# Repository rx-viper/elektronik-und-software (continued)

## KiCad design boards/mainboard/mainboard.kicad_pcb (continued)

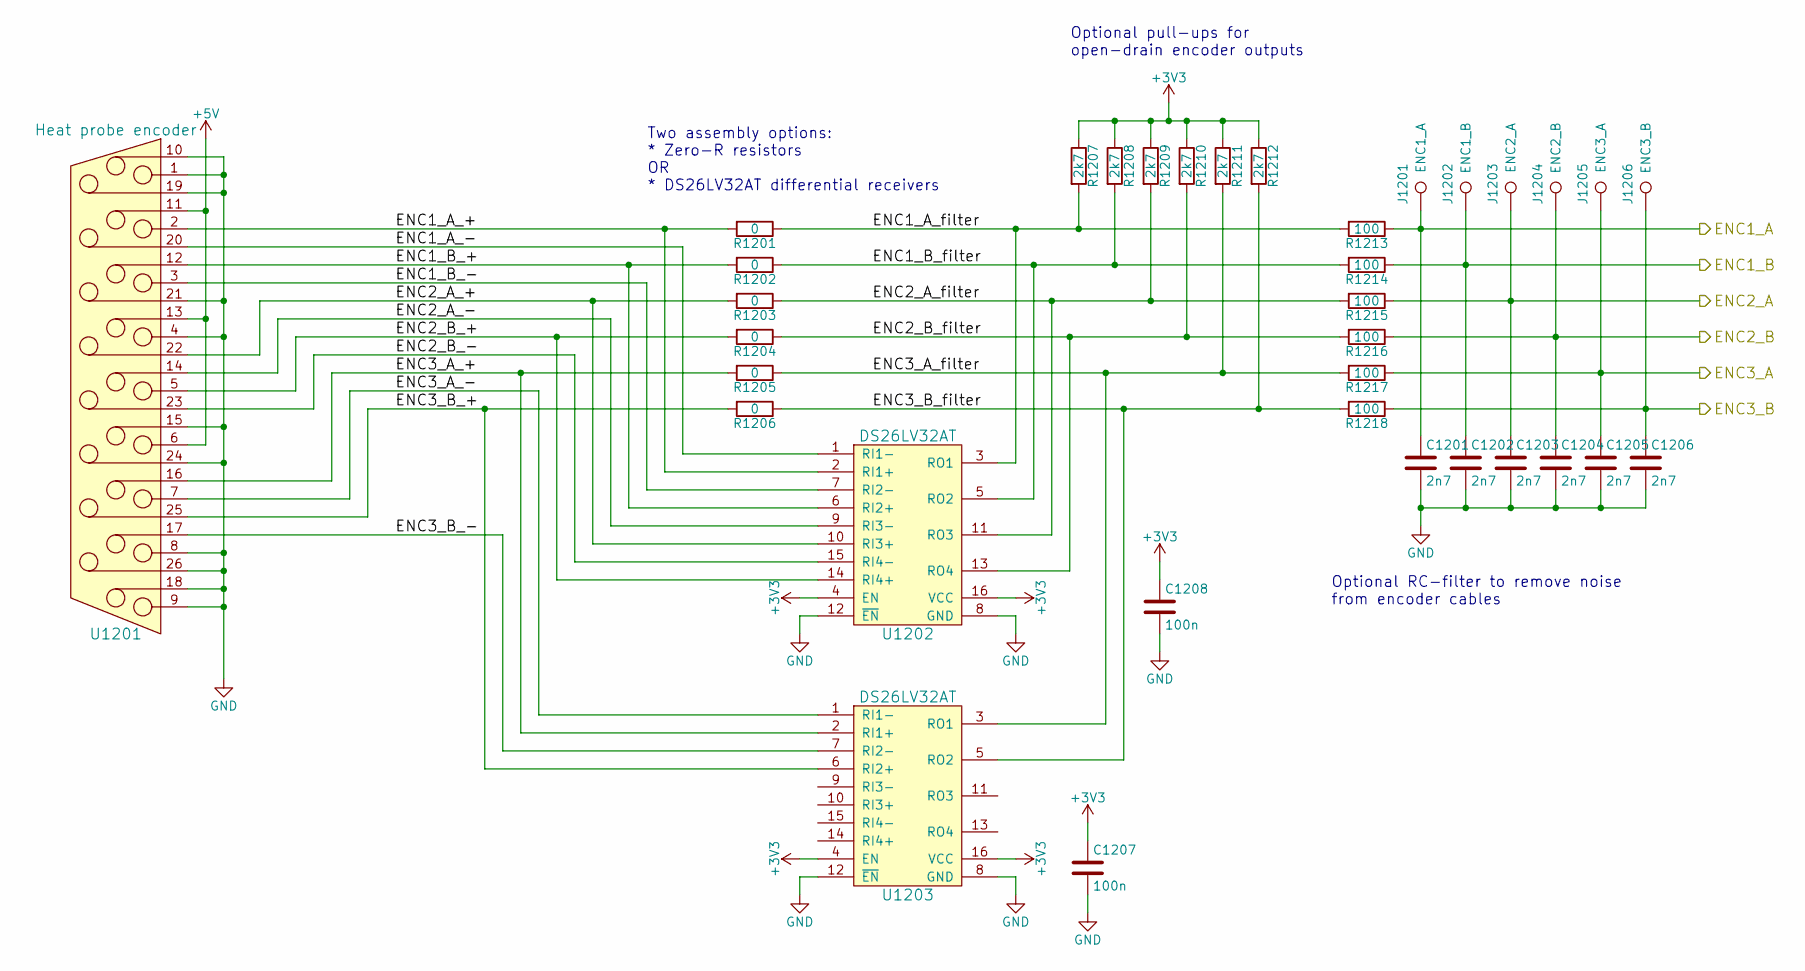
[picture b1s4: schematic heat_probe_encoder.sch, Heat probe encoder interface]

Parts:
C1201, C1202, C1203, C1204, C1205, C1206: 2n7; C_0603
C1207, C1208: 100n; C_0603
J1201: ENC1_A; Measurement_Point_Round-SMD-Pad_Small
J1202: ENC1_B; Measurement_Point_Round-SMD-Pad_Small
J1203: ENC2_A; Measurement_Point_Round-SMD-Pad_Small
J1204: ENC2_B; Measurement_Point_Round-SMD-Pad_Small
J1205: ENC3_A; Measurement_Point_Round-SMD-Pad_Small
J1206: ENC3_B; Measurement_Point_Round-SMD-Pad_Small
R1201, R1202, R1203, R1204, R1205, R1206: 0; R_0603
R1207, R1208, R1209, R1210, R1211, R1212: 2k7; R_0603
R1213, R1214, R1215, R1216, R1217, R1218: 100; R_0603
U1201: Heat probe encoder; D-Sub_HD_26_F
U1202, U1203: DS26LV32AT; SOIC-16_3.9x9.9mm_Pitch1.27mm

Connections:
+3V3: C1207.1, C1208.1, R1207.1, R1208.1, R1209.1, R1210.1, R1211.1, R1212.1, U1202.4 (EN), U1202.16 (VCC), U1203.4 (EN), U1203.16 (VCC); also elsewhere on the board
+5V: U1201.6, U1201.11, U1201.13; also elsewhere on the board
/Heat_Probe_Encoder/ENC1_A: C1201.1, J1201.1, R1213.1; also elsewhere on the board
/Heat_Probe_Encoder/ENC1_A_+: R1201.2, U1201.2, U1202.2 (RI1+)
/Heat_Probe_Encoder/ENC1_A_-: U1201.20, U1202.1 (RI1-)
/Heat_Probe_Encoder/ENC1_A_filter: R1201.1, R1207.2, R1213.2, U1202.3 (RO1)
/Heat_Probe_Encoder/ENC1_B: C1202.1, J1202.1, R1214.1; also elsewhere on the board
/Heat_Probe_Encoder/ENC1_B_+: R1202.2, U1201.12, U1202.6 (RI2+)
/Heat_Probe_Encoder/ENC1_B_-: U1201.3, U1202.7 (RI2-)
/Heat_Probe_Encoder/ENC1_B_filter: R1202.1, R1208.2, R1214.2, U1202.5 (RO2)
/Heat_Probe_Encoder/ENC2_A: C1203.1, J1203.1, R1215.1; also elsewhere on the board
/Heat_Probe_Encoder/ENC2_A_+: R1203.2, U1201.22, U1202.10 (RI3+)
/Heat_Probe_Encoder/ENC2_A_-: U1201.14, U1202.9 (RI3-)
/Heat_Probe_Encoder/ENC2_A_filter: R1203.1, R1209.2, R1215.2, U1202.11 (RO3)
/Heat_Probe_Encoder/ENC2_B: C1204.1, J1204.1, R1216.1; also elsewhere on the board
/Heat_Probe_Encoder/ENC2_B_+: R1204.2, U1201.5, U1202.14 (RI4+)
/Heat_Probe_Encoder/ENC2_B_-: U1201.23, U1202.15 (RI4-)
/Heat_Probe_Encoder/ENC2_B_filter: R1204.1, R1210.2, R1216.2, U1202.13 (RO4)
/Heat_Probe_Encoder/ENC3_A: C1205.1, J1205.1, R1217.1; also elsewhere on the board
/Heat_Probe_Encoder/ENC3_A_+: R1205.2, U1201.16, U1203.2 (RI1+)
/Heat_Probe_Encoder/ENC3_A_-: U1201.7, U1203.1 (RI1-)
/Heat_Probe_Encoder/ENC3_A_filter: R1205.1, R1211.2, R1217.2, U1203.3 (RO1)
/Heat_Probe_Encoder/ENC3_B: C1206.1, J1206.1, R1218.1; also elsewhere on the board
/Heat_Probe_Encoder/ENC3_B_+: R1206.2, U1201.25, U1203.6 (RI2+)
/Heat_Probe_Encoder/ENC3_B_-: U1201.17, U1203.7 (RI2-)
/Heat_Probe_Encoder/ENC3_B_filter: R1206.1, R1212.2, R1218.2, U1203.5 (RO2)
GND: C1201.2, C1202.2, C1203.2, C1204.2, C1205.2, C1206.2, C1207.2, C1208.2, U1201.1, U1201.4, U1201.8, U1201.9, U1201.10, U1201.15, U1201.18, U1201.19, U1201.21, U1201.24, U1201.26, U1202.8 (GND), U1202.12 (~EN), U1203.8 (GND), U1203.12 (~EN); also elsewhere on the board

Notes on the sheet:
Optional pull-ups for open-drain encoder outputs
Optional RC-filter to remove noise from encoder cables
Two assembly options: * Zero-R resistors OR * DS26LV32AT differential receivers

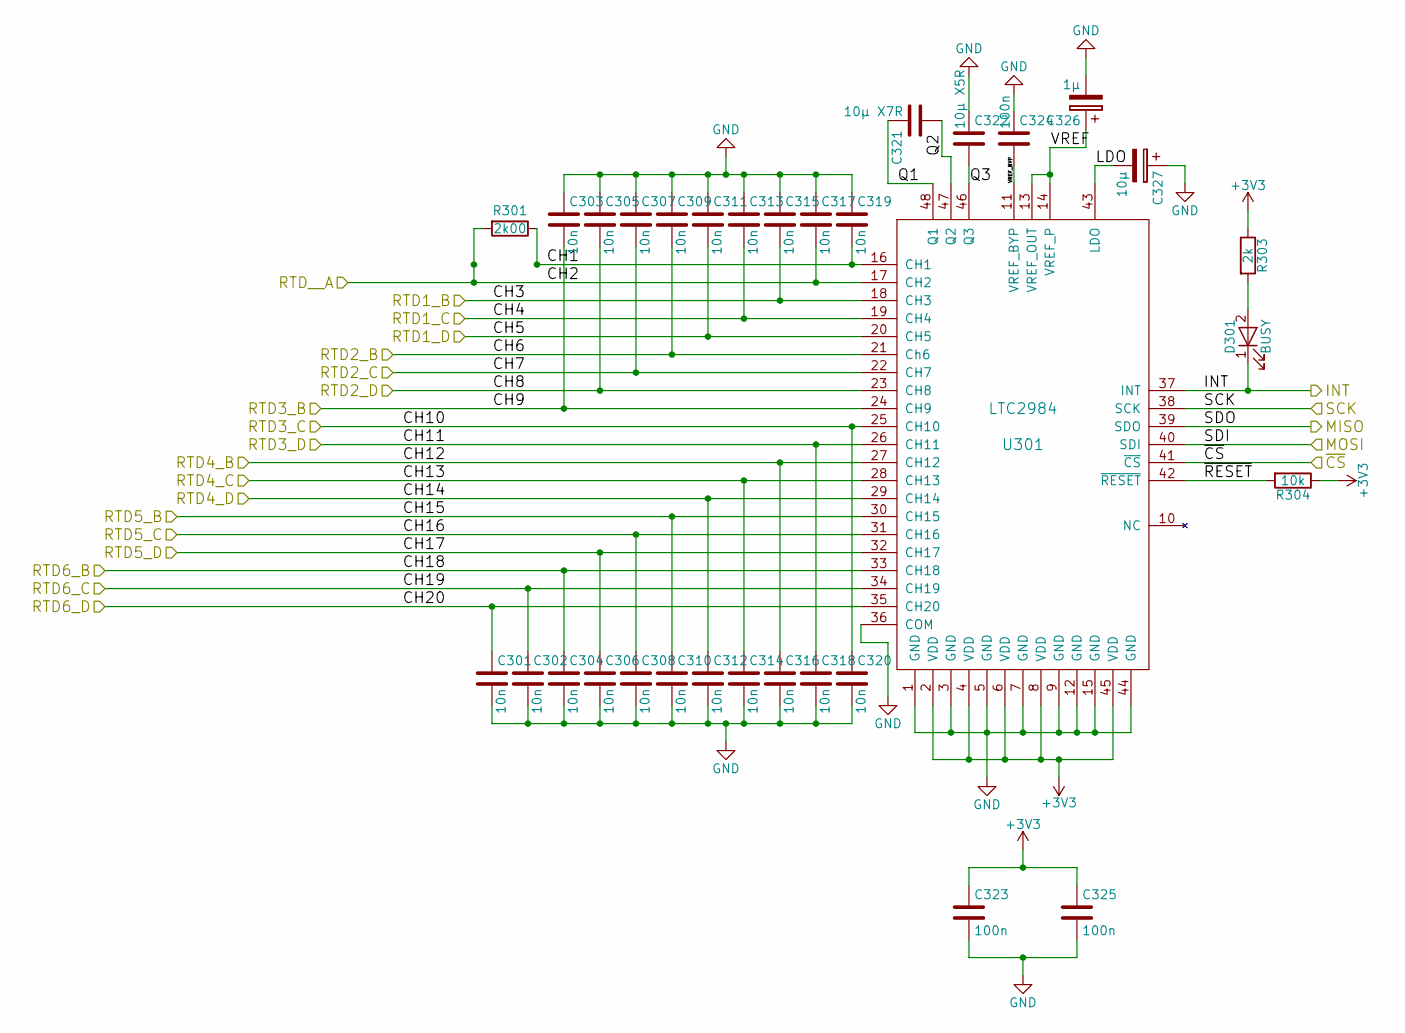
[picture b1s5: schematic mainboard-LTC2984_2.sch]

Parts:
C301, C302, C303, C304, C305, C306, C307, C308, C309, C310, C311, C312, C313, C314, C315, C316, C317, C318, C319, C320: 10n; C_0603
C321: 10µ X7R; C_0805
C322: 10µ X5R; C_0805
C323, C324, C325: 100n; C_0603
C326: 1µ; C_0805
C327: 10µ; C_0805
D301: BUSY; LED_0603
R301: 2k00; R_1206
R303: 2k; R_0603
R304: 10k; R_0603
U301: LTC2984; LQFP-48_7x7mm_Pitch0.5mm

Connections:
+3V3: C323.1, C325.1, R303.1, R304.1, U301.2 (VDD), U301.4 (VDD), U301.6 (VDD), U301.8 (VDD), U301.45 (VDD); also elsewhere on the board
/Mainboard_Temp_Sensors/INT2: D301.1 (K), U301.37 (INT)
/Mainboard_Temp_Sensors/Mainboard_LTC2984_2/CH1: C319.2, R301.1, U301.16 (CH1)
/Mainboard_Temp_Sensors/Mainboard_LTC2984_2/LDO: C327.2, U301.43 (LDO)
/Mainboard_Temp_Sensors/Mainboard_LTC2984_2/Q1: C321.2, U301.48 (Q1)
/Mainboard_Temp_Sensors/Mainboard_LTC2984_2/Q2: C321.1, U301.47 (Q2)
/Mainboard_Temp_Sensors/Mainboard_LTC2984_2/Q3: C322.2, U301.46 (Q3)
/Mainboard_Temp_Sensors/Mainboard_LTC2984_2/VREF: C326.1, U301.13 (VREF_OUT), U301.14 (VREF_P)
/Mainboard_Temp_Sensors/Mainboard_LTC2984_2/VREF_BYP: C324.2, U301.11 (VREF_BYP)
/Mainboard_Temp_Sensors/Mainboard_LTC2984_2/~RESET: R304.2, U301.42 (~RESET)
/Mainboard_Temp_Sensors/SPI1_CS2: U301.41 (~CS); also elsewhere on the board
/Mainboard_Temp_Sensors/SPI1_MISO: U301.39 (SDO); also elsewhere on the board
/Mainboard_Temp_Sensors/SPI1_MOSI: U301.40 (SDI); also elsewhere on the board
/Mainboard_Temp_Sensors/SPI1_SCK: U301.38 (SCK); also elsewhere on the board
/Mainboard_Temp_Sensors/T2_RTD1_A: C317.2, R301.2, U301.17 (CH2); also elsewhere on the board
/Mainboard_Temp_Sensors/T2_RTD1_B: C315.2, U301.18 (CH3); also elsewhere on the board
/Mainboard_Temp_Sensors/T2_RTD1_C: C313.2, U301.19 (CH4); also elsewhere on the board
/Mainboard_Temp_Sensors/T2_RTD1_D: C311.2, U301.20 (CH5); also elsewhere on the board
/Mainboard_Temp_Sensors/T2_RTD2_B: C309.2, U301.21 (Ch6); also elsewhere on the board
/Mainboard_Temp_Sensors/T2_RTD2_C: C307.2, U301.22 (CH7); also elsewhere on the board
/Mainboard_Temp_Sensors/T2_RTD2_D: C305.2, U301.23 (CH8); also elsewhere on the board
/Mainboard_Temp_Sensors/T2_RTD3_B: C303.2, U301.24 (CH9); also elsewhere on the board
/Mainboard_Temp_Sensors/T2_RTD3_C: C320.1, U301.25 (CH10); also elsewhere on the board
/Mainboard_Temp_Sensors/T2_RTD3_D: C318.1, U301.26 (CH11); also elsewhere on the board
/Mainboard_Temp_Sensors/T2_RTD4_B: C316.1, U301.27 (CH12); also elsewhere on the board
/Mainboard_Temp_Sensors/T2_RTD4_C: C314.1, U301.28 (CH13); also elsewhere on the board
/Mainboard_Temp_Sensors/T2_RTD4_D: C312.1, U301.29 (CH14); also elsewhere on the board
/Mainboard_Temp_Sensors/T2_RTD5_B: C310.1, U301.30 (CH15); also elsewhere on the board
/Mainboard_Temp_Sensors/T2_RTD5_C: C308.1, U301.31 (CH16); also elsewhere on the board
/Mainboard_Temp_Sensors/T2_RTD5_D: C306.1, U301.32 (CH17); also elsewhere on the board
/Mainboard_Temp_Sensors/T2_RTD6_B: C304.1, U301.33 (CH18); also elsewhere on the board
/Mainboard_Temp_Sensors/T2_RTD6_C: C302.1, U301.34 (CH19); also elsewhere on the board
/Mainboard_Temp_Sensors/T2_RTD6_D: C301.1, U301.35 (CH20); also elsewhere on the board
GND: C301.2, C302.2, C303.1, C304.2, C305.1, C306.2, C307.1, C308.2, C309.1, C310.2, C311.1, C312.2, C313.1, C314.2, C315.1, C316.2, C317.1, C318.2, C319.1, C320.2, C322.1, C323.2, C324.1, C325.2, C326.2, C327.1, U301.1 (GND), U301.3 (GND), U301.5 (GND), U301.7 (GND), U301.9 (GND), U301.12 (GND), U301.15 (GND), U301.36 (COM), U301.44 (GND); also elsewhere on the board
unnamed: D301.2 (A), R303.2

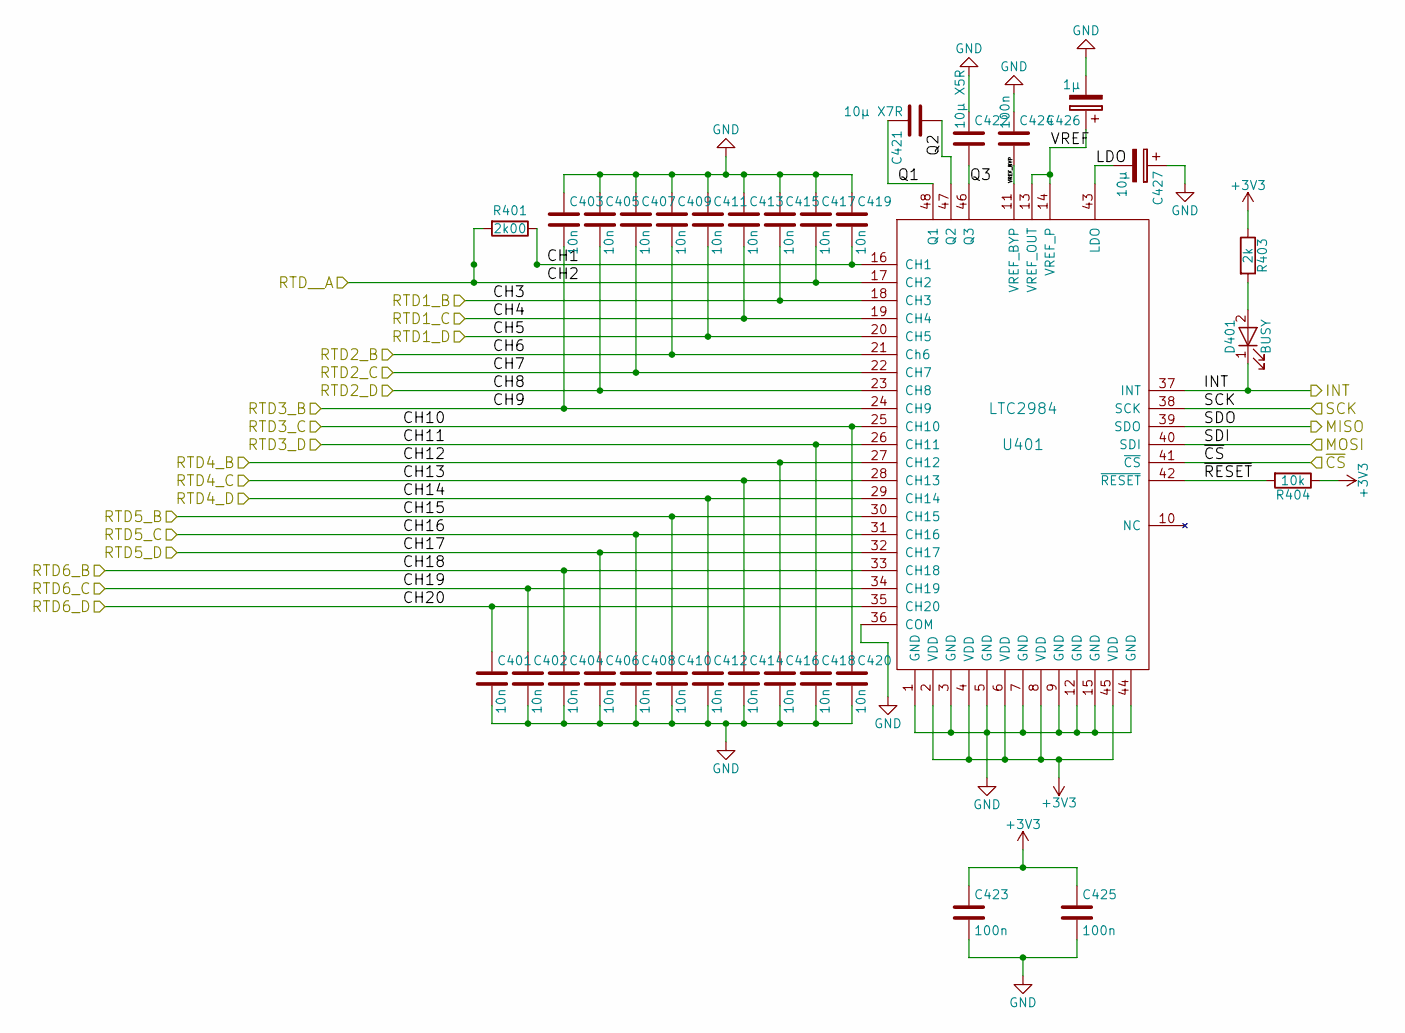
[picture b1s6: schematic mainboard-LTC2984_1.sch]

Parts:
C401, C402, C403, C404, C405, C406, C407, C408, C409, C410, C411, C412, C413, C414, C415, C416, C417, C418, C419, C420: 10n; C_0603
C421: 10µ X7R; C_0805
C422: 10µ X5R; C_0805
C423, C424, C425: 100n; C_0603
C426: 1µ; C_0805
C427: 10µ; C_0805
D401: BUSY; LED_0603
R401: 2k00; R_1206
R403: 2k; R_0603
R404: 10k; R_0603
U401: LTC2984; LQFP-48_7x7mm_Pitch0.5mm

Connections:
+3V3: C423.1, C425.1, R403.1, R404.1, U401.2 (VDD), U401.4 (VDD), U401.6 (VDD), U401.8 (VDD), U401.45 (VDD); also elsewhere on the board
/Mainboard_Temp_Sensors/INT1: D401.1 (K), U401.37 (INT)
/Mainboard_Temp_Sensors/Mainboard_LTC2984_1/CH1: C419.2, R401.1, U401.16 (CH1)
/Mainboard_Temp_Sensors/Mainboard_LTC2984_1/LDO: C427.2, U401.43 (LDO)
/Mainboard_Temp_Sensors/Mainboard_LTC2984_1/Q1: C421.2, U401.48 (Q1)
/Mainboard_Temp_Sensors/Mainboard_LTC2984_1/Q2: C421.1, U401.47 (Q2)
/Mainboard_Temp_Sensors/Mainboard_LTC2984_1/Q3: C422.2, U401.46 (Q3)
/Mainboard_Temp_Sensors/Mainboard_LTC2984_1/VREF: C426.1, U401.13 (VREF_OUT), U401.14 (VREF_P)
/Mainboard_Temp_Sensors/Mainboard_LTC2984_1/VREF_BYP: C424.2, U401.11 (VREF_BYP)
/Mainboard_Temp_Sensors/Mainboard_LTC2984_1/~RESET: R404.2, U401.42 (~RESET)
/Mainboard_Temp_Sensors/SPI1_CS1: U401.41 (~CS); also elsewhere on the board
/Mainboard_Temp_Sensors/SPI1_MISO: U401.39 (SDO); also elsewhere on the board
/Mainboard_Temp_Sensors/SPI1_MOSI: U401.40 (SDI); also elsewhere on the board
/Mainboard_Temp_Sensors/SPI1_SCK: U401.38 (SCK); also elsewhere on the board
/Mainboard_Temp_Sensors/T1_RTD1_A: C417.2, R401.2, U401.17 (CH2); also elsewhere on the board
/Mainboard_Temp_Sensors/T1_RTD1_B: C415.2, U401.18 (CH3); also elsewhere on the board
/Mainboard_Temp_Sensors/T1_RTD1_C: C413.2, U401.19 (CH4); also elsewhere on the board
/Mainboard_Temp_Sensors/T1_RTD1_D: C411.2, U401.20 (CH5); also elsewhere on the board
/Mainboard_Temp_Sensors/T1_RTD2_B: C409.2, U401.21 (Ch6); also elsewhere on the board
/Mainboard_Temp_Sensors/T1_RTD2_C: C407.2, U401.22 (CH7); also elsewhere on the board
/Mainboard_Temp_Sensors/T1_RTD2_D: C405.2, U401.23 (CH8); also elsewhere on the board
/Mainboard_Temp_Sensors/T1_RTD3_B: C403.2, U401.24 (CH9); also elsewhere on the board
/Mainboard_Temp_Sensors/T1_RTD3_C: C420.1, U401.25 (CH10); also elsewhere on the board
/Mainboard_Temp_Sensors/T1_RTD3_D: C418.1, U401.26 (CH11); also elsewhere on the board
/Mainboard_Temp_Sensors/T1_RTD4_B: C416.1, U401.27 (CH12); also elsewhere on the board
/Mainboard_Temp_Sensors/T1_RTD4_C: C414.1, U401.28 (CH13); also elsewhere on the board
/Mainboard_Temp_Sensors/T1_RTD4_D: C412.1, U401.29 (CH14); also elsewhere on the board
/Mainboard_Temp_Sensors/T1_RTD5_B: C410.1, U401.30 (CH15); also elsewhere on the board
/Mainboard_Temp_Sensors/T1_RTD5_C: C408.1, U401.31 (CH16); also elsewhere on the board
/Mainboard_Temp_Sensors/T1_RTD5_D: C406.1, U401.32 (CH17); also elsewhere on the board
/Mainboard_Temp_Sensors/T1_RTD6_B: C404.1, U401.33 (CH18); also elsewhere on the board
/Mainboard_Temp_Sensors/T1_RTD6_C: C402.1, U401.34 (CH19); also elsewhere on the board
/Mainboard_Temp_Sensors/T1_RTD6_D: C401.1, U401.35 (CH20); also elsewhere on the board
GND: C401.2, C402.2, C403.1, C404.2, C405.1, C406.2, C407.1, C408.2, C409.1, C410.2, C411.1, C412.2, C413.1, C414.2, C415.1, C416.2, C417.1, C418.2, C419.1, C420.2, C422.1, C423.2, C424.1, C425.2, C426.2, C427.1, U401.1 (GND), U401.3 (GND), U401.5 (GND), U401.7 (GND), U401.9 (GND), U401.12 (GND), U401.15 (GND), U401.36 (COM), U401.44 (GND); also elsewhere on the board
unnamed: D401.2 (A), R403.2

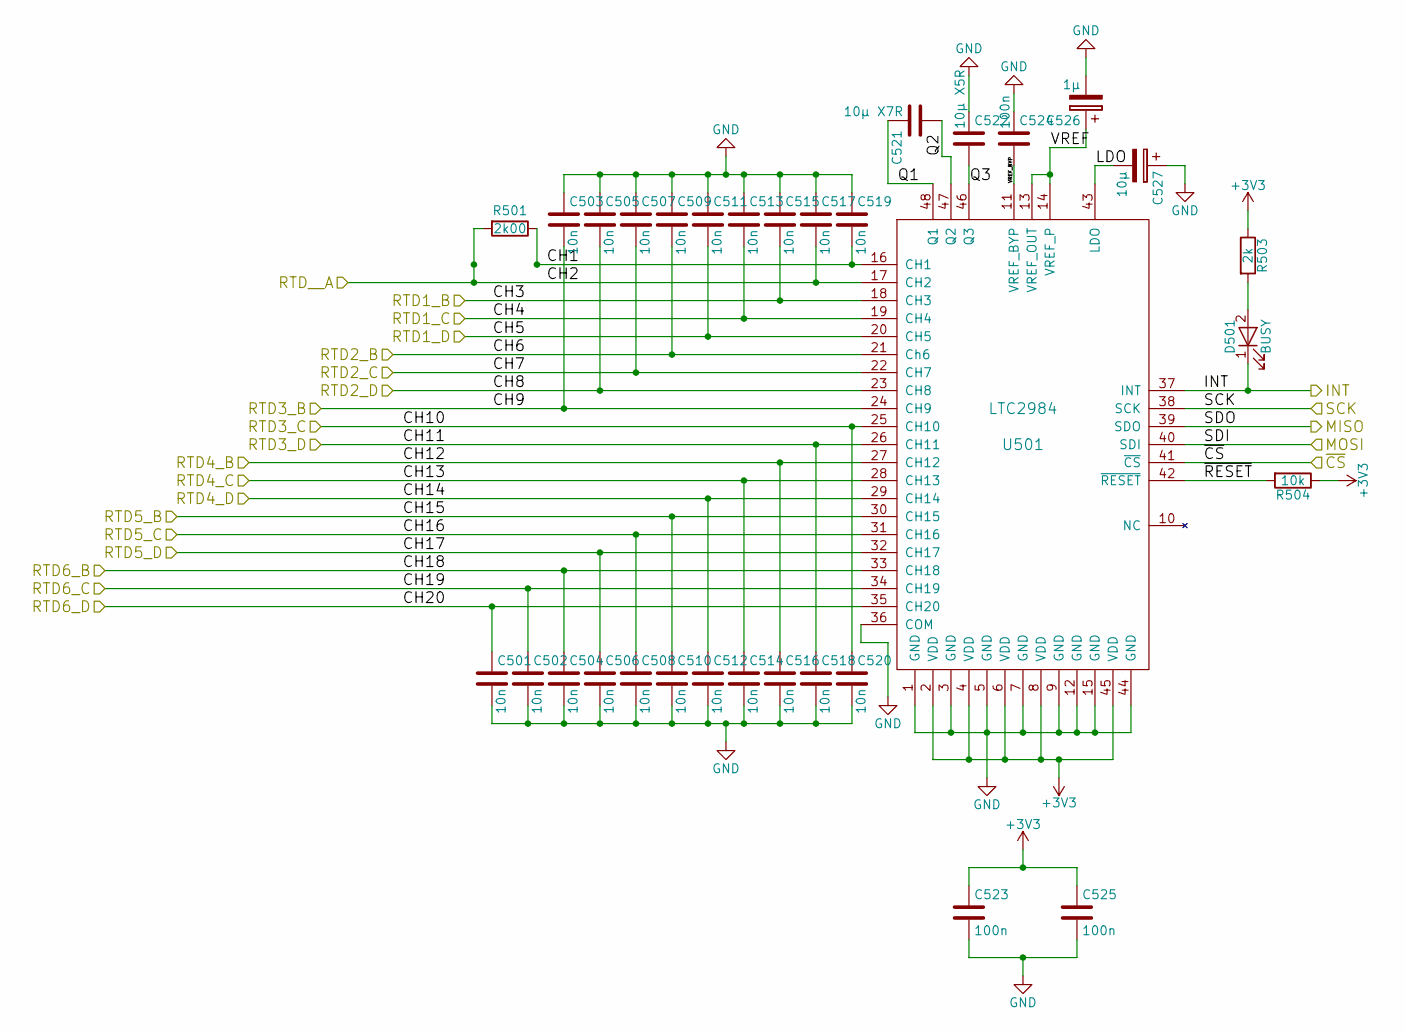
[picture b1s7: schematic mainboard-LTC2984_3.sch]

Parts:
C501, C502, C503, C504, C505, C506, C507, C508, C509, C510, C511, C512, C513, C514, C515, C516, C517, C518, C519, C520: 10n; C_0603
C521: 10µ X7R; C_0805
C522: 10µ X5R; C_0805
C523, C524, C525: 100n; C_0603
C526: 1µ; C_0805
C527: 10µ; C_0805
D501: BUSY; LED_0603
R501: 2k00; R_1206
R503: 2k; R_0603
R504: 10k; R_0603
U501: LTC2984; LQFP-48_7x7mm_Pitch0.5mm

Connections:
+3V3: C523.1, C525.1, R503.1, R504.1, U501.2 (VDD), U501.4 (VDD), U501.6 (VDD), U501.8 (VDD), U501.45 (VDD); also elsewhere on the board
/Mainboard_Temp_Sensors/INT3: D501.1 (K), U501.37 (INT)
/Mainboard_Temp_Sensors/Mainboard_LTC2984_3/CH1: C519.2, R501.1, U501.16 (CH1)
/Mainboard_Temp_Sensors/Mainboard_LTC2984_3/LDO: C527.2, U501.43 (LDO)
/Mainboard_Temp_Sensors/Mainboard_LTC2984_3/Q1: C521.2, U501.48 (Q1)
/Mainboard_Temp_Sensors/Mainboard_LTC2984_3/Q2: C521.1, U501.47 (Q2)
/Mainboard_Temp_Sensors/Mainboard_LTC2984_3/Q3: C522.2, U501.46 (Q3)
/Mainboard_Temp_Sensors/Mainboard_LTC2984_3/VREF: C526.1, U501.13 (VREF_OUT), U501.14 (VREF_P)
/Mainboard_Temp_Sensors/Mainboard_LTC2984_3/VREF_BYP: C524.2, U501.11 (VREF_BYP)
/Mainboard_Temp_Sensors/Mainboard_LTC2984_3/~RESET: R504.2, U501.42 (~RESET)
/Mainboard_Temp_Sensors/SPI1_CS3: U501.41 (~CS); also elsewhere on the board
/Mainboard_Temp_Sensors/SPI1_MISO: U501.39 (SDO); also elsewhere on the board
/Mainboard_Temp_Sensors/SPI1_MOSI: U501.40 (SDI); also elsewhere on the board
/Mainboard_Temp_Sensors/SPI1_SCK: U501.38 (SCK); also elsewhere on the board
/Mainboard_Temp_Sensors/T3_RTD1_A: C517.2, R501.2, U501.17 (CH2); also elsewhere on the board
/Mainboard_Temp_Sensors/T3_RTD1_B: C515.2, U501.18 (CH3); also elsewhere on the board
/Mainboard_Temp_Sensors/T3_RTD1_C: C513.2, U501.19 (CH4); also elsewhere on the board
/Mainboard_Temp_Sensors/T3_RTD1_D: C511.2, U501.20 (CH5); also elsewhere on the board
/Mainboard_Temp_Sensors/T3_RTD2_B: C509.2, U501.21 (Ch6); also elsewhere on the board
/Mainboard_Temp_Sensors/T3_RTD2_C: C507.2, U501.22 (CH7); also elsewhere on the board
/Mainboard_Temp_Sensors/T3_RTD2_D: C505.2, U501.23 (CH8); also elsewhere on the board
/Mainboard_Temp_Sensors/T3_RTD3_B: C503.2, U501.24 (CH9); also elsewhere on the board
/Mainboard_Temp_Sensors/T3_RTD3_C: C520.1, U501.25 (CH10); also elsewhere on the board
/Mainboard_Temp_Sensors/T3_RTD3_D: C518.1, U501.26 (CH11); also elsewhere on the board
/Mainboard_Temp_Sensors/T3_RTD4_B: C516.1, U501.27 (CH12); also elsewhere on the board
/Mainboard_Temp_Sensors/T3_RTD4_C: C514.1, U501.28 (CH13); also elsewhere on the board
/Mainboard_Temp_Sensors/T3_RTD4_D: C512.1, U501.29 (CH14); also elsewhere on the board
/Mainboard_Temp_Sensors/T3_RTD5_B: C510.1, U501.30 (CH15); also elsewhere on the board
/Mainboard_Temp_Sensors/T3_RTD5_C: C508.1, U501.31 (CH16); also elsewhere on the board
/Mainboard_Temp_Sensors/T3_RTD5_D: C506.1, U501.32 (CH17); also elsewhere on the board
/Mainboard_Temp_Sensors/T3_RTD6_B: C504.1, U501.33 (CH18); also elsewhere on the board
/Mainboard_Temp_Sensors/T3_RTD6_C: C502.1, U501.34 (CH19); also elsewhere on the board
/Mainboard_Temp_Sensors/T3_RTD6_D: C501.1, U501.35 (CH20); also elsewhere on the board
GND: C501.2, C502.2, C503.1, C504.2, C505.1, C506.2, C507.1, C508.2, C509.1, C510.2, C511.1, C512.2, C513.1, C514.2, C515.1, C516.2, C517.1, C518.2, C519.1, C520.2, C522.1, C523.2, C524.1, C525.2, C526.2, C527.1, U501.1 (GND), U501.3 (GND), U501.5 (GND), U501.7 (GND), U501.9 (GND), U501.12 (GND), U501.15 (GND), U501.36 (COM), U501.44 (GND); also elsewhere on the board
unnamed: D501.2 (A), R503.2

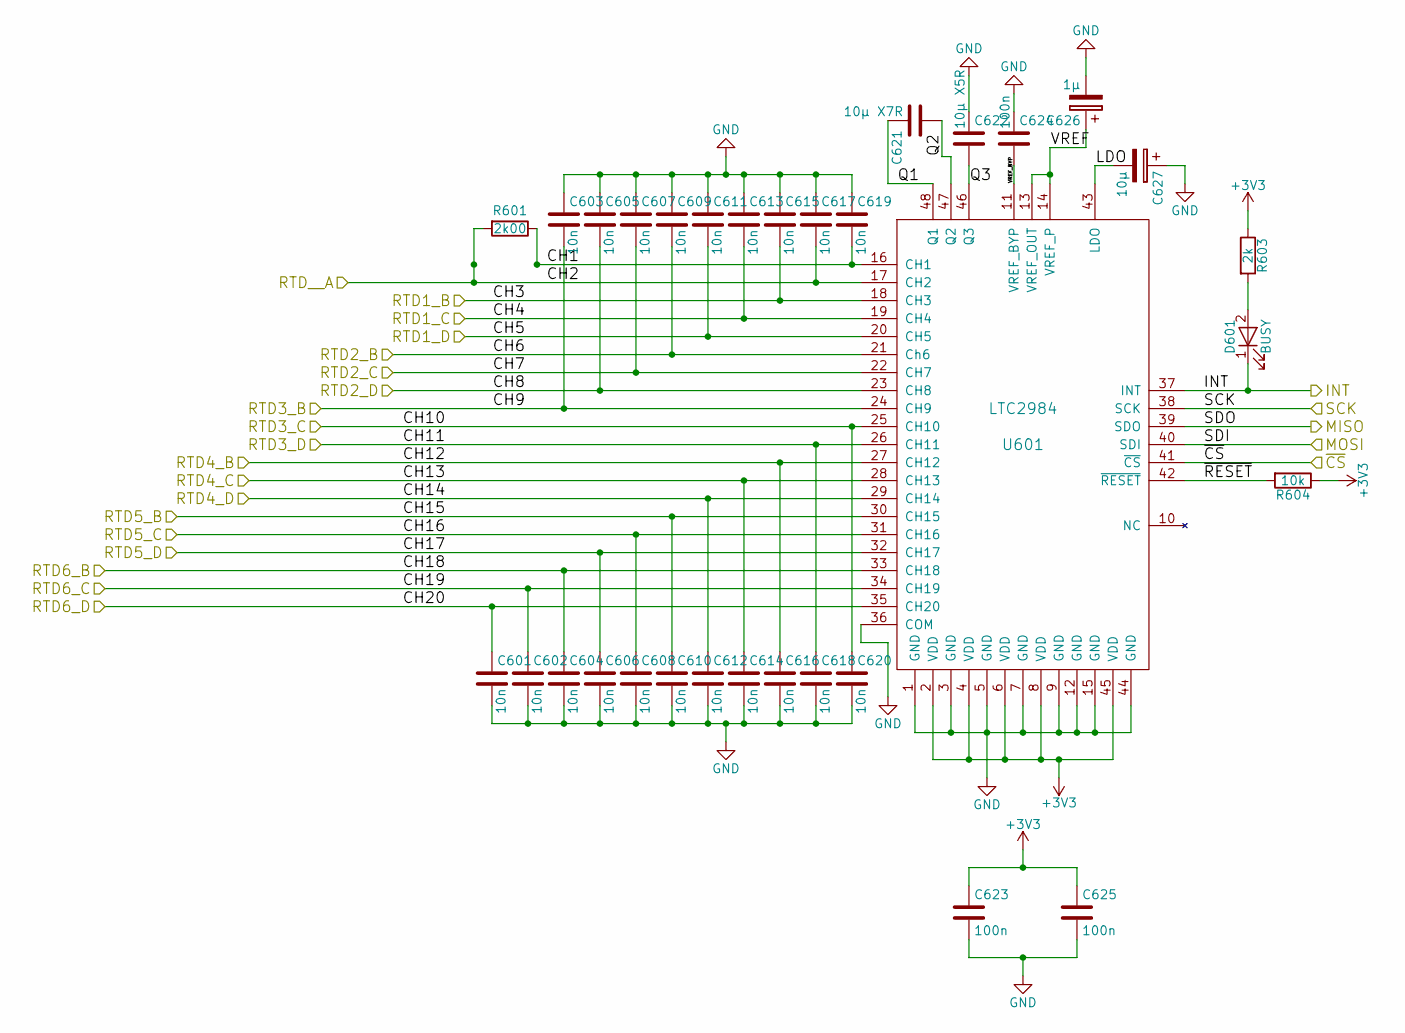
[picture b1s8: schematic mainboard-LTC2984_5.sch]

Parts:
C601, C602, C603, C604, C605, C606, C607, C608, C609, C610, C611, C612, C613, C614, C615, C616, C617, C618, C619, C620: 10n; C_0603
C621: 10µ X7R; C_0805
C622: 10µ X5R; C_0805
C623, C624, C625: 100n; C_0603
C626: 1µ; C_0805
C627: 10µ; C_0805
D601: BUSY; LED_0603
R601: 2k00; R_1206
R603: 2k; R_0603
R604: 10k; R_0603
U601: LTC2984; LQFP-48_7x7mm_Pitch0.5mm

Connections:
+3V3: C623.1, C625.1, R603.1, R604.1, U601.2 (VDD), U601.4 (VDD), U601.6 (VDD), U601.8 (VDD), U601.45 (VDD); also elsewhere on the board
/Mainboard_Temp_Sensors/INT5: D601.1 (K), U601.37 (INT)
/Mainboard_Temp_Sensors/Mainboard_LTC2984_5/CH1: C619.2, R601.1, U601.16 (CH1)
/Mainboard_Temp_Sensors/Mainboard_LTC2984_5/LDO: C627.2, U601.43 (LDO)
/Mainboard_Temp_Sensors/Mainboard_LTC2984_5/Q1: C621.2, U601.48 (Q1)
/Mainboard_Temp_Sensors/Mainboard_LTC2984_5/Q2: C621.1, U601.47 (Q2)
/Mainboard_Temp_Sensors/Mainboard_LTC2984_5/Q3: C622.2, U601.46 (Q3)
/Mainboard_Temp_Sensors/Mainboard_LTC2984_5/VREF: C626.1, U601.13 (VREF_OUT), U601.14 (VREF_P)
/Mainboard_Temp_Sensors/Mainboard_LTC2984_5/VREF_BYP: C624.2, U601.11 (VREF_BYP)
/Mainboard_Temp_Sensors/Mainboard_LTC2984_5/~RESET: R604.2, U601.42 (~RESET)
/Mainboard_Temp_Sensors/SPI2_CS2: U601.41 (~CS); also elsewhere on the board
/Mainboard_Temp_Sensors/SPI2_MISO: U601.39 (SDO); also elsewhere on the board
/Mainboard_Temp_Sensors/SPI2_MOSI: U601.40 (SDI); also elsewhere on the board
/Mainboard_Temp_Sensors/SPI2_SCK: U601.38 (SCK); also elsewhere on the board
/Mainboard_Temp_Sensors/T5_RTD1_A: C617.2, R601.2, U601.17 (CH2); also elsewhere on the board
/Mainboard_Temp_Sensors/T5_RTD1_B: C615.2, U601.18 (CH3); also elsewhere on the board
/Mainboard_Temp_Sensors/T5_RTD1_C: C613.2, U601.19 (CH4); also elsewhere on the board
/Mainboard_Temp_Sensors/T5_RTD1_D: C611.2, U601.20 (CH5); also elsewhere on the board
/Mainboard_Temp_Sensors/T5_RTD2_B: C609.2, U601.21 (Ch6); also elsewhere on the board
/Mainboard_Temp_Sensors/T5_RTD2_C: C607.2, U601.22 (CH7); also elsewhere on the board
/Mainboard_Temp_Sensors/T5_RTD2_D: C605.2, U601.23 (CH8); also elsewhere on the board
/Mainboard_Temp_Sensors/T5_RTD3_B: C603.2, U601.24 (CH9); also elsewhere on the board
/Mainboard_Temp_Sensors/T5_RTD3_C: C620.1, U601.25 (CH10); also elsewhere on the board
/Mainboard_Temp_Sensors/T5_RTD3_D: C618.1, U601.26 (CH11); also elsewhere on the board
/Mainboard_Temp_Sensors/T5_RTD4_B: C616.1, U601.27 (CH12); also elsewhere on the board
/Mainboard_Temp_Sensors/T5_RTD4_C: C614.1, U601.28 (CH13); also elsewhere on the board
/Mainboard_Temp_Sensors/T5_RTD4_D: C612.1, U601.29 (CH14); also elsewhere on the board
/Mainboard_Temp_Sensors/T5_RTD5_B: C610.1, U601.30 (CH15); also elsewhere on the board
/Mainboard_Temp_Sensors/T5_RTD5_C: C608.1, U601.31 (CH16); also elsewhere on the board
/Mainboard_Temp_Sensors/T5_RTD5_D: C606.1, U601.32 (CH17); also elsewhere on the board
/Mainboard_Temp_Sensors/T5_RTD6_B: C604.1, U601.33 (CH18); also elsewhere on the board
/Mainboard_Temp_Sensors/T5_RTD6_C: C602.1, U601.34 (CH19); also elsewhere on the board
/Mainboard_Temp_Sensors/T5_RTD6_D: C601.1, U601.35 (CH20); also elsewhere on the board
GND: C601.2, C602.2, C603.1, C604.2, C605.1, C606.2, C607.1, C608.2, C609.1, C610.2, C611.1, C612.2, C613.1, C614.2, C615.1, C616.2, C617.1, C618.2, C619.1, C620.2, C622.1, C623.2, C624.1, C625.2, C626.2, C627.1, U601.1 (GND), U601.3 (GND), U601.5 (GND), U601.7 (GND), U601.9 (GND), U601.12 (GND), U601.15 (GND), U601.36 (COM), U601.44 (GND); also elsewhere on the board
unnamed: D601.2 (A), R603.2

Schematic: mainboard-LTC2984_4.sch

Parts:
C701, C702, C703, C704, C705, C706, C707, C708, C709, C710, C712, C714, C716, C717, C718, C719, C720: 10n; C_0603
C721: 10µ X7R; C_0805
C722: 10µ X5R; C_0805
C723, C724, C725: 100n; C_0603
C726: 1µ; C_0805
C727: 10µ; C_0805
D701: BUSY; LED_0603
R701: 2k00; R_1206
R703: 2k; R_0603
R704: 10k; R_0603
U701: LTC2984; LQFP-48_7x7mm_Pitch0.5mm

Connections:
+3V3: C723.1, C725.1, R703.1, R704.1, U701.2 (VDD), U701.4 (VDD), U701.6 (VDD), U701.8 (VDD), U701.45 (VDD); also elsewhere on the board
/Mainboard_Temp_Sensors/INT4: D701.1 (K), U701.37 (INT)
/Mainboard_Temp_Sensors/Mainboard_LTC2984_4/CH1: C719.2, R701.1, U701.16 (CH1)
/Mainboard_Temp_Sensors/Mainboard_LTC2984_4/LDO: C727.2, U701.43 (LDO)
/Mainboard_Temp_Sensors/Mainboard_LTC2984_4/Q1: C721.2, U701.48 (Q1)
/Mainboard_Temp_Sensors/Mainboard_LTC2984_4/Q2: C721.1, U701.47 (Q2)
/Mainboard_Temp_Sensors/Mainboard_LTC2984_4/Q3: C722.2, U701.46 (Q3)
/Mainboard_Temp_Sensors/Mainboard_LTC2984_4/VREF: C726.1, U701.13 (VREF_OUT), U701.14 (VREF_P)
/Mainboard_Temp_Sensors/Mainboard_LTC2984_4/VREF_BYP: C724.2, U701.11 (VREF_BYP)
/Mainboard_Temp_Sensors/Mainboard_LTC2984_4/~RESET: R704.2, U701.42 (~RESET)
/Mainboard_Temp_Sensors/SPI2_CS1: U701.41 (~CS); also elsewhere on the board
/Mainboard_Temp_Sensors/SPI2_MISO: U701.39 (SDO); also elsewhere on the board
/Mainboard_Temp_Sensors/SPI2_MOSI: U701.40 (SDI); also elsewhere on the board
/Mainboard_Temp_Sensors/SPI2_SCK: U701.38 (SCK); also elsewhere on the board
/Mainboard_Temp_Sensors/T4_RTD1_A: C717.2, R701.2, U701.17 (CH2); also elsewhere on the board
/Mainboard_Temp_Sensors/T4_RTD2_B: C709.2, U701.21 (Ch6); also elsewhere on the board
/Mainboard_Temp_Sensors/T4_RTD2_C: C707.2, U701.22 (CH7); also elsewhere on the board
/Mainboard_Temp_Sensors/T4_RTD2_D: C705.2, U701.23 (CH8); also elsewhere on the board
/Mainboard_Temp_Sensors/T4_RTD3_B: C703.2, U701.24 (CH9); also elsewhere on the board
/Mainboard_Temp_Sensors/T4_RTD3_C: C720.1, U701.25 (CH10); also elsewhere on the board
/Mainboard_Temp_Sensors/T4_RTD3_D: C718.1, U701.26 (CH11); also elsewhere on the board
/Mainboard_Temp_Sensors/T4_RTD4_B: C716.1, U701.27 (CH12); also elsewhere on the board
/Mainboard_Temp_Sensors/T4_RTD4_C: C714.1, U701.28 (CH13); also elsewhere on the board
/Mainboard_Temp_Sensors/T4_RTD4_D: C712.1, U701.29 (CH14); also elsewhere on the board
/Mainboard_Temp_Sensors/T4_RTD5_B: C710.1, U701.30 (CH15); also elsewhere on the board
/Mainboard_Temp_Sensors/T4_RTD5_C: C708.1, U701.31 (CH16); also elsewhere on the board
/Mainboard_Temp_Sensors/T4_RTD5_D: C706.1, U701.32 (CH17); also elsewhere on the board
/Mainboard_Temp_Sensors/T4_RTD6_B: C704.1, U701.33 (CH18); also elsewhere on the board
/Mainboard_Temp_Sensors/T4_RTD6_C: C702.1, U701.34 (CH19); also elsewhere on the board
/Mainboard_Temp_Sensors/T4_RTD6_D: C701.1, U701.35 (CH20); also elsewhere on the board
GND: C701.2, C702.2, C703.1, C704.2, C705.1, C706.2, C707.1, C708.2, C709.1, C710.2, C712.2, C714.2, C716.2, C717.1, C718.2, C719.1, C720.2, C722.1, C723.2, C724.1, C725.2, C726.2, C727.1, U701.1 (GND), U701.3 (GND), U701.5 (GND), U701.7 (GND), U701.9 (GND), U701.12 (GND), U701.15 (GND), U701.36 (COM), U701.44 (GND); also elsewhere on the board
unnamed: D701.2 (A), R703.2

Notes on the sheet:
T4_RTD1 is not connected in the first PCB revision

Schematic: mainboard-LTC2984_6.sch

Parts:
C801, C802, C803, C804, C805, C806, C807, C808, C809, C810, C811, C812, C813, C814, C815, C816, C817, C818, C819, C820: 10n; C_0603
C821: 10µ X7R; C_0805
C822: 10µ X5R; C_0805
C823, C824, C825: 100n; C_0603
C826: 1µ; C_0805
C827: 10µ; C_0805
D801: BUSY; LED_0603
R801: 2k00; R_1206
R803: 2k; R_0603
R804: 10k; R_0603
U801: LTC2984; LQFP-48_7x7mm_Pitch0.5mm

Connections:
+3V3: C823.1, C825.1, R803.1, R804.1, U801.2 (VDD), U801.4 (VDD), U801.6 (VDD), U801.8 (VDD), U801.45 (VDD); also elsewhere on the board
/Mainboard_Temp_Sensors/INT6: D801.1 (K), U801.37 (INT)
/Mainboard_Temp_Sensors/Mainboard_LTC2984_6/CH1: C819.2, R801.1, U801.16 (CH1)
/Mainboard_Temp_Sensors/Mainboard_LTC2984_6/LDO: C827.2, U801.43 (LDO)
/Mainboard_Temp_Sensors/Mainboard_LTC2984_6/Q1: C821.2, U801.48 (Q1)
/Mainboard_Temp_Sensors/Mainboard_LTC2984_6/Q2: C821.1, U801.47 (Q2)
/Mainboard_Temp_Sensors/Mainboard_LTC2984_6/Q3: C822.2, U801.46 (Q3)
/Mainboard_Temp_Sensors/Mainboard_LTC2984_6/VREF: C826.1, U801.13 (VREF_OUT), U801.14 (VREF_P)
/Mainboard_Temp_Sensors/Mainboard_LTC2984_6/VREF_BYP: C824.2, U801.11 (VREF_BYP)
/Mainboard_Temp_Sensors/Mainboard_LTC2984_6/~RESET: R804.2, U801.42 (~RESET)
/Mainboard_Temp_Sensors/SPI2_CS3: U801.41 (~CS); also elsewhere on the board
/Mainboard_Temp_Sensors/SPI2_MISO: U801.39 (SDO); also elsewhere on the board
/Mainboard_Temp_Sensors/SPI2_MOSI: U801.40 (SDI); also elsewhere on the board
/Mainboard_Temp_Sensors/SPI2_SCK: U801.38 (SCK); also elsewhere on the board
/Mainboard_Temp_Sensors/T6_RTD1_A: C817.2, R801.2, U801.17 (CH2); also elsewhere on the board
/Mainboard_Temp_Sensors/T6_RTD1_B: C815.2, U801.18 (CH3); also elsewhere on the board
/Mainboard_Temp_Sensors/T6_RTD1_C: C813.2, U801.19 (CH4); also elsewhere on the board
/Mainboard_Temp_Sensors/T6_RTD1_D: C811.2, U801.20 (CH5); also elsewhere on the board
/Mainboard_Temp_Sensors/T6_RTD2_B: C809.2, U801.21 (Ch6); also elsewhere on the board
/Mainboard_Temp_Sensors/T6_RTD2_C: C807.2, U801.22 (CH7); also elsewhere on the board
/Mainboard_Temp_Sensors/T6_RTD2_D: C805.2, U801.23 (CH8); also elsewhere on the board
/Mainboard_Temp_Sensors/T6_RTD3_B: C803.2, U801.24 (CH9); also elsewhere on the board
/Mainboard_Temp_Sensors/T6_RTD3_C: C820.1, U801.25 (CH10); also elsewhere on the board
/Mainboard_Temp_Sensors/T6_RTD3_D: C818.1, U801.26 (CH11); also elsewhere on the board
/Mainboard_Temp_Sensors/T6_RTD4_B: C816.1, U801.27 (CH12); also elsewhere on the board
/Mainboard_Temp_Sensors/T6_RTD4_C: C814.1, U801.28 (CH13); also elsewhere on the board
/Mainboard_Temp_Sensors/T6_RTD4_D: C812.1, U801.29 (CH14); also elsewhere on the board
/Mainboard_Temp_Sensors/T6_RTD5_B: C810.1, U801.30 (CH15); also elsewhere on the board
/Mainboard_Temp_Sensors/T6_RTD5_C: C808.1, U801.31 (CH16); also elsewhere on the board
/Mainboard_Temp_Sensors/T6_RTD5_D: C806.1, U801.32 (CH17); also elsewhere on the board
/Mainboard_Temp_Sensors/T6_RTD6_B: C804.1, U801.33 (CH18); also elsewhere on the board
/Mainboard_Temp_Sensors/T6_RTD6_C: C802.1, U801.34 (CH19); also elsewhere on the board
/Mainboard_Temp_Sensors/T6_RTD6_D: C801.1, U801.35 (CH20); also elsewhere on the board
GND: C801.2, C802.2, C803.1, C804.2, C805.1, C806.2, C807.1, C808.2, C809.1, C810.2, C811.1, C812.2, C813.1, C814.2, C815.1, C816.2, C817.1, C818.2, C819.1, C820.2, C822.1, C823.2, C824.1, C825.2, C826.2, C827.1, U801.1 (GND), U801.3 (GND), U801.5 (GND), U801.7 (GND), U801.9 (GND), U801.12 (GND), U801.15 (GND), U801.36 (COM), U801.44 (GND); also elsewhere on the board
unnamed: D801.2 (A), R803.2

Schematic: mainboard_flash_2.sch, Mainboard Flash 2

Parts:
C1001: 100n; C_0603
J1001: FL2_CS; Measurement_Point_Round-SMD-Pad_Small
J1002: FL2_SCK; Measurement_Point_Round-SMD-Pad_Small
J1003: FL2_MISO; Measurement_Point_Round-SMD-Pad_Small
J1004: FL2_MOSI; Measurement_Point_Round-SMD-Pad_Small
U1001: SST26VF064B; SOIJ-8_5.3x5.3mm_Pitch1.27mm

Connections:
+3V3: C1001.1, U1001.3 (WP), U1001.7 (HOLD), U1001.8 (VDD); also elsewhere on the board
/Mainboard microcontroller/Mainboard_Flash_2/CS: J1001.1, U1001.1 (CE); also elsewhere on the board
/Mainboard microcontroller/Mainboard_Flash_2/MISO: J1003.1, U1001.2 (SO); also elsewhere on the board
/Mainboard microcontroller/Mainboard_Flash_2/MOSI: J1004.1, U1001.5 (SI); also elsewhere on the board
/Mainboard microcontroller/Mainboard_Flash_2/SCK: J1002.1, U1001.6 (SCK); also elsewhere on the board
GND: C1001.2, U1001.4 (Vss); also elsewhere on the board
